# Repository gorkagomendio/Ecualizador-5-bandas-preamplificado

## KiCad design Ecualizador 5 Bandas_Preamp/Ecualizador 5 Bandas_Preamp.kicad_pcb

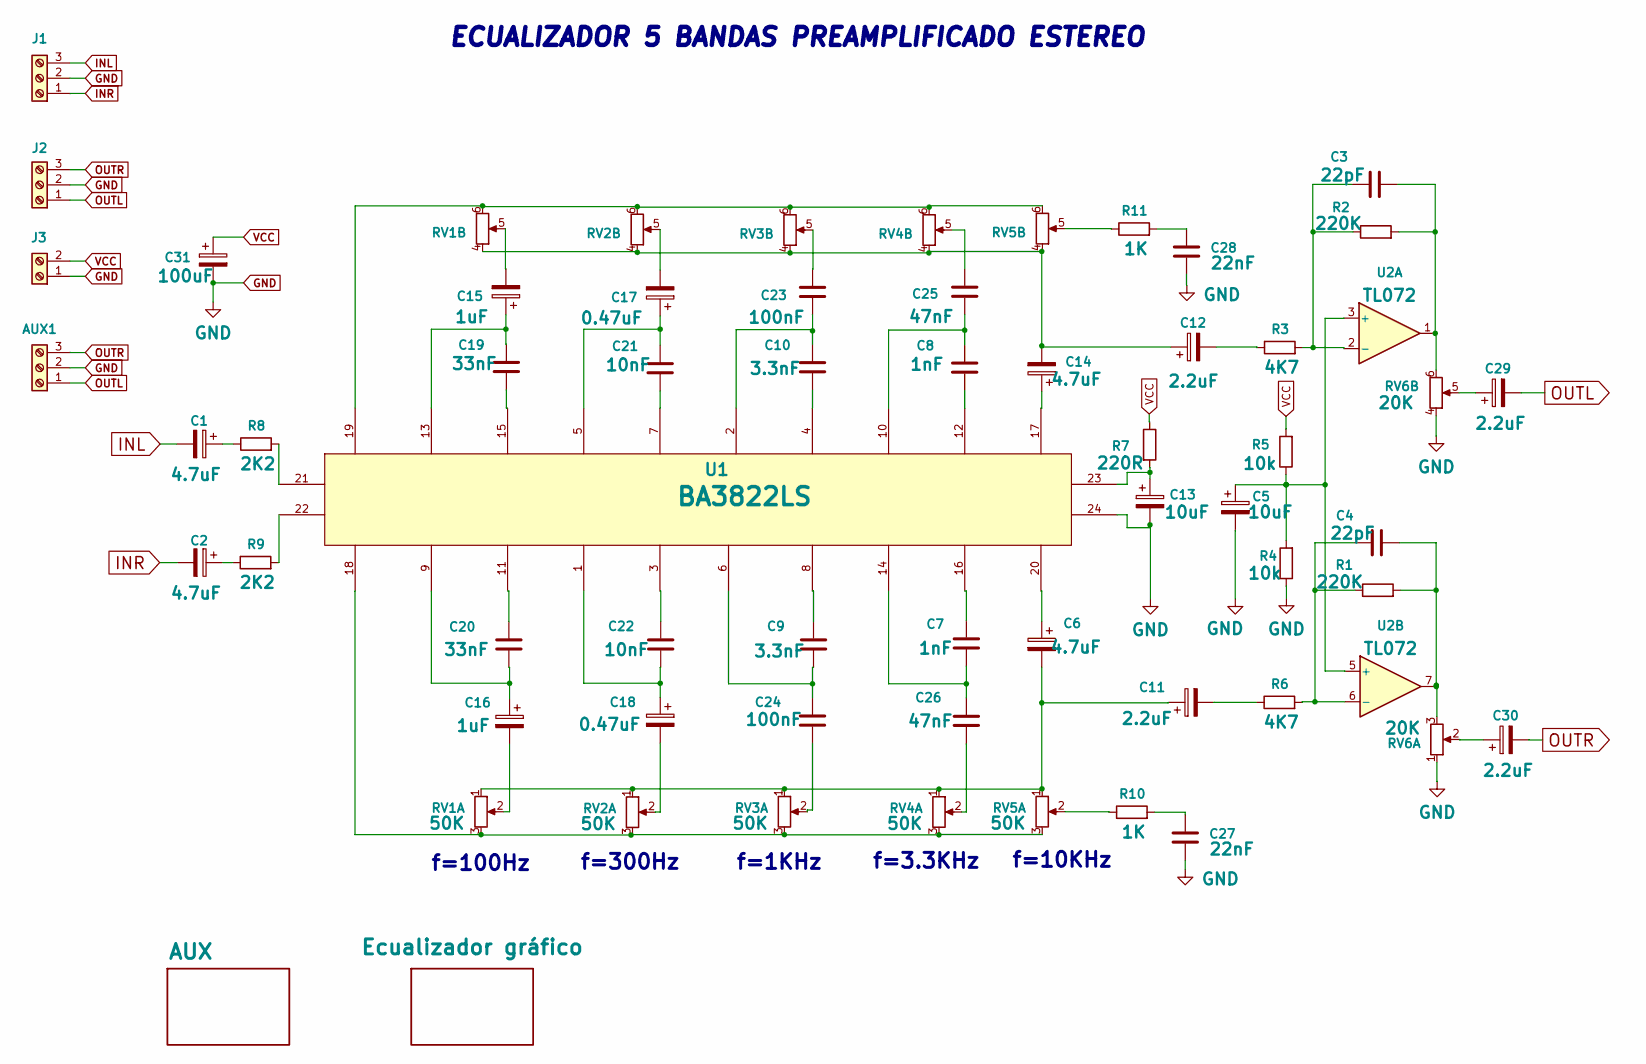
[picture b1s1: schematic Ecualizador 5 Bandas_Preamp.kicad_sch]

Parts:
AUX1: Screw_Terminal_01x03; JST_XH_B3B-XH-AM_1x03_P2.50mm_Vertical
C1, C2, C6, C14: 4.7uF; CP_Radial_D5.0mm_P2.50mm
C3, C4: 22pF; C_1206_3216Metric
C5, C13: 10uF; CP_Radial_D5.0mm_P2.00mm
C7, C8: 1nF; C_1206_3216Metric
C9, C10: 3.3nF; C_1206_3216Metric
C11, C12, C29, C30: 2.2uF; CP_Radial_D5.0mm_P2.00mm
C15, C16: 1uF; CP_Radial_D5.0mm_P2.00mm
C17, C18: 0.47uF; CP_Radial_D5.0mm_P2.00mm
C19, C20: 33nF; C_1206_3216Metric
C21, C22: 10nF; C_1206_3216Metric
C23, C24: 100nF; C_1206_3216Metric
C25, C26: 47nF; C_1206_3216Metric
C27, C28: 22nF; C_1206_3216Metric
C31: 100uF; CP_Radial_D6.3mm_P2.50mm
J1, J2: Screw_Terminal_01x03; JST_XH_B3B-XH-AM_1x03_P2.50mm_Vertical
J3: Screw_Terminal_01x02; TerminalBlock_bornier-2_P5.08mm
R1, R2: 220K; R_1206_3216Metric
R3, R6: 4K7; R_1206_3216Metric
R4, R5: 10k; R_1206_3216Metric
R7: 220R; R_1206_3216Metric
R8, R9: 2K2; R_1206_3216Metric
R10, R11: 1K; R_1206_3216Metric
RV1, RV2, RV3, RV4, RV5: 50K; Pot_Deslizante_Fader
RV6: 20K; Pot_Deslizante_Fader_Corto
U1: BA3822LS
U2: TL072; SO-8_3.9x4.9mm_P1.27mm

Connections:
GND: AUX1.2, C5.2, C13.2, C27.2, C28.2, C31.2, J1.2, J2.2, J3.1, R4.1, RV6.1, RV6.4, U1.24, U2.4 (V-)
INL: C1.2, J1.3
INR: C2.2, J1.1
unnamed: C1.1, R8.1
unnamed: C2.1, R9.1
unnamed: C3.1, R2.2, RV6.6, U2.1
unnamed: C4.1, R1.2, RV6.3, U2.7
unnamed: C6.1, U1.20
unnamed: C7.1, U1.16
unnamed: C8.2, U1.12
unnamed: C9.1, U1.8
unnamed: C10.1, C23.2, U1.2
unnamed: C10.2, U1.4
unnamed: C6.2, C11.1, RV1.1, RV2.1, RV3.1, RV4.1, RV5.1
unnamed: C11.2, R6.1
unnamed: C12.1, C14.2, RV1.4, RV2.4, RV3.4, RV4.4, RV5.4
unnamed: C12.2, R3.1
unnamed: C13.1, R7.2, U1.23
unnamed: C14.1, U1.17
unnamed: C15.1, C19.1, U1.13
unnamed: C15.2, RV1.5
unnamed: C16.1, C20.2, U1.9
unnamed: C16.2, RV1.2
unnamed: C17.1, C21.1, U1.5
unnamed: C17.2, RV2.5
unnamed: C18.1, C22.2, U1.1
unnamed: C18.2, RV2.2
unnamed: C19.2, U1.15
unnamed: C20.1, U1.11
unnamed: C21.2, U1.7
unnamed: C22.1, U1.3
unnamed: C23.1, RV3.5
unnamed: C9.2, C24.1, U1.6
unnamed: C24.2, RV3.2
unnamed: C25.1, RV4.5
unnamed: C8.1, C25.2, U1.10
unnamed: C7.2, C26.1, U1.14
unnamed: C26.2, RV4.2
unnamed: C27.1, R10.2
unnamed: C28.1, R11.2
unnamed: C29.1, RV6.5
unnamed: C30.1, RV6.2
unnamed: R8.2, U1.21
unnamed: R9.2, U1.22
unnamed: R10.1, RV5.2
unnamed: R11.1, RV5.5
unnamed: RV1.3, RV2.3, RV3.3, RV4.3, RV5.3, U1.18
unnamed: RV1.6, RV2.6, RV3.6, RV4.6, RV5.6, U1.19
unnamed: C5.1, R4.2, R5.1, U2.3 (+), U2.5 (+)
unnamed: C3.2, R2.1, R3.2, U2.2 (-)
unnamed: C4.2, R1.1, R6.2, U2.6 (-)
OUTL: AUX1.1, C29.2, J2.1
OUTR: AUX1.3, C30.2, J2.3
VCC: C31.1, J3.2, R5.2, R7.1, U2.8 (V+)

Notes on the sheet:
ECUALIZADOR 5 BANDAS PREAMPLIFICADO ESTEREO
f=100Hz
f=10KHz
f=3.3KHz
f=300Hz
f=1KHz

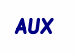
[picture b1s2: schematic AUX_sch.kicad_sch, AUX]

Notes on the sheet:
AUX

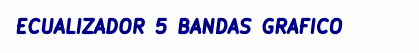
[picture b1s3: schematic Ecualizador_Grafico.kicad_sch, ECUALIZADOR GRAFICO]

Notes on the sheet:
ECUALIZADOR 5 BANDAS GRAFICO

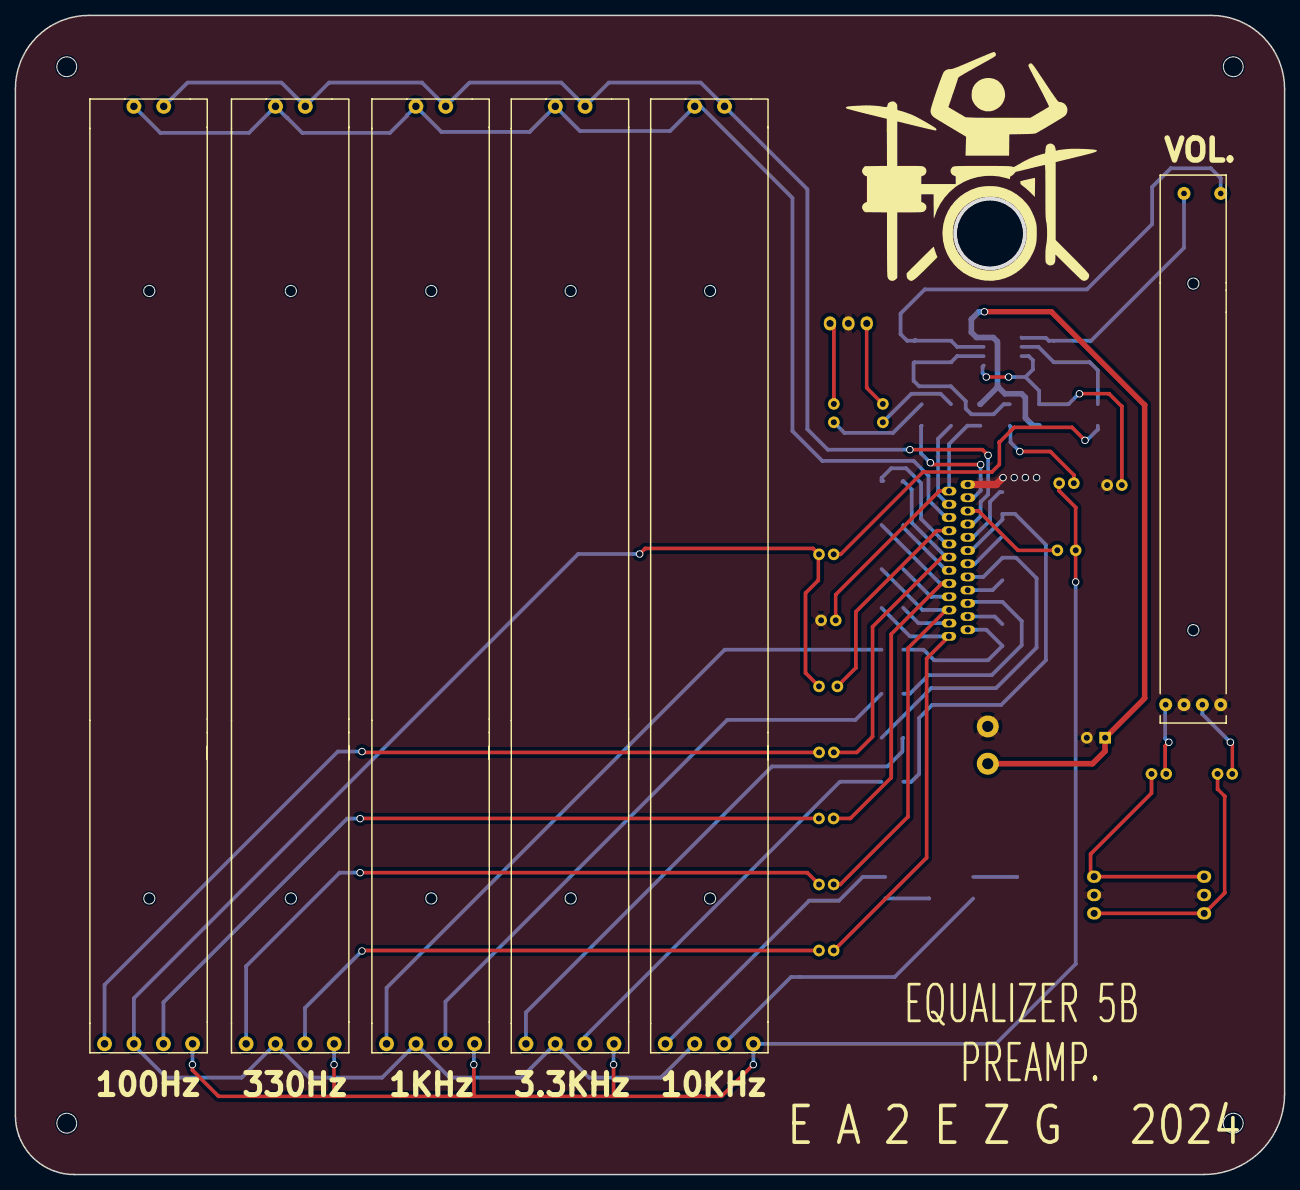
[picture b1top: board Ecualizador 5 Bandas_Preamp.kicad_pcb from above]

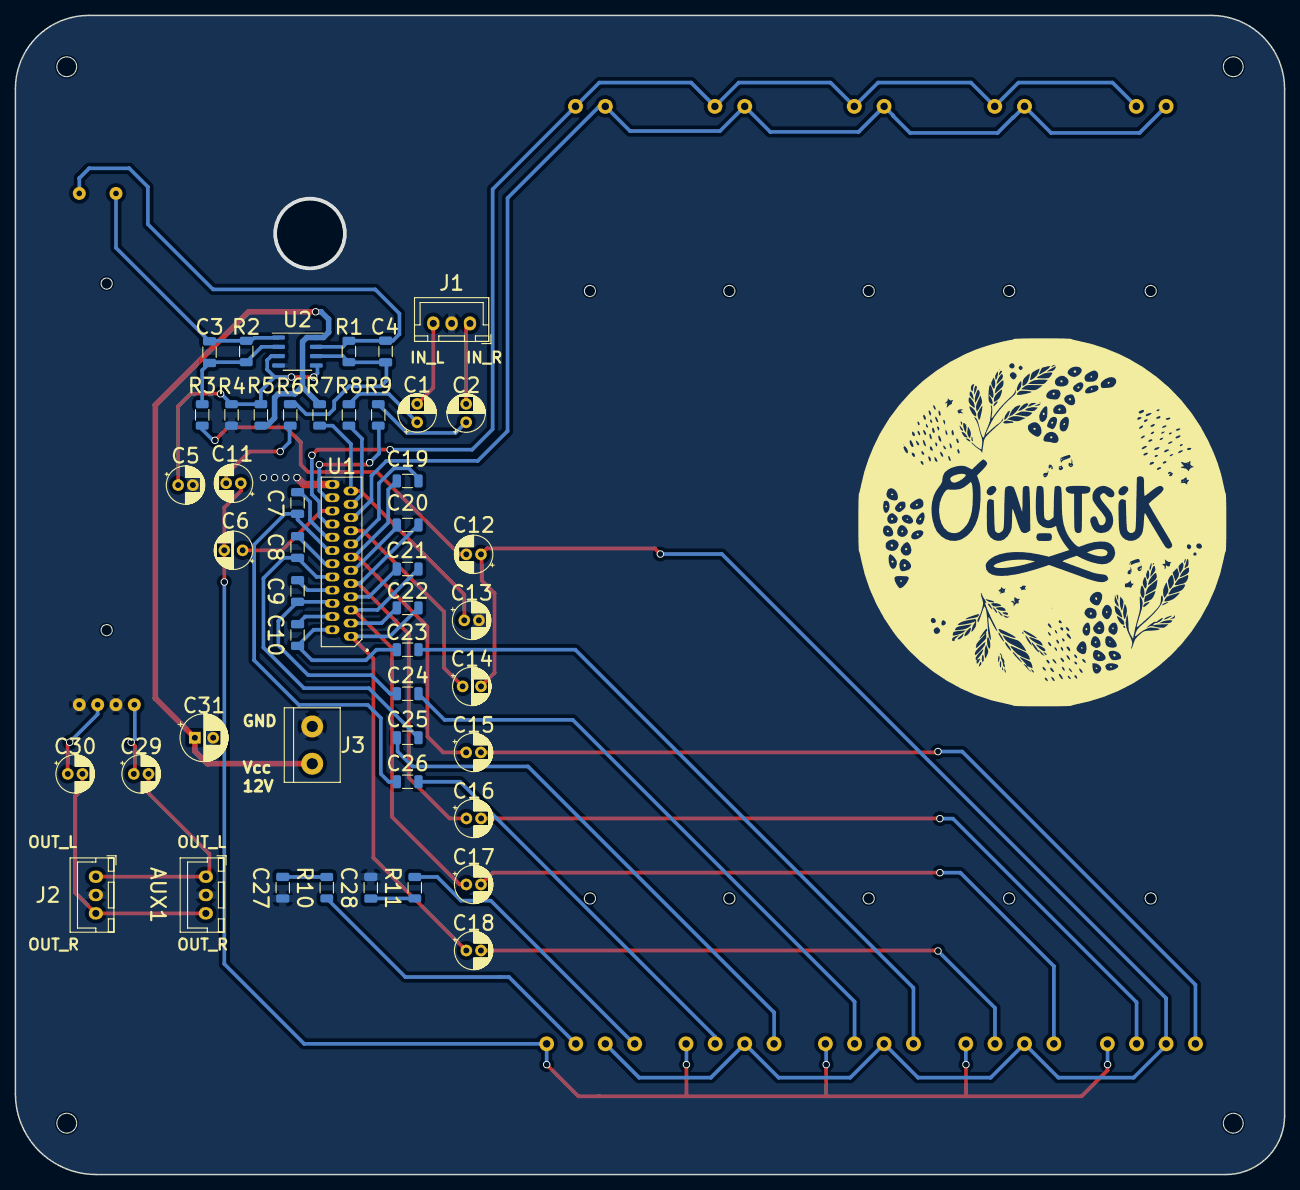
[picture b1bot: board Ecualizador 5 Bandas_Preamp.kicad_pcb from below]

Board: 2 copper layers, 173.0 x 158.0 mm, 58 parts (48 on the bottom side), 54 nets.

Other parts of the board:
REF1, REF2, REF3, REF4: MountingHole_2.7mm_M2.5
